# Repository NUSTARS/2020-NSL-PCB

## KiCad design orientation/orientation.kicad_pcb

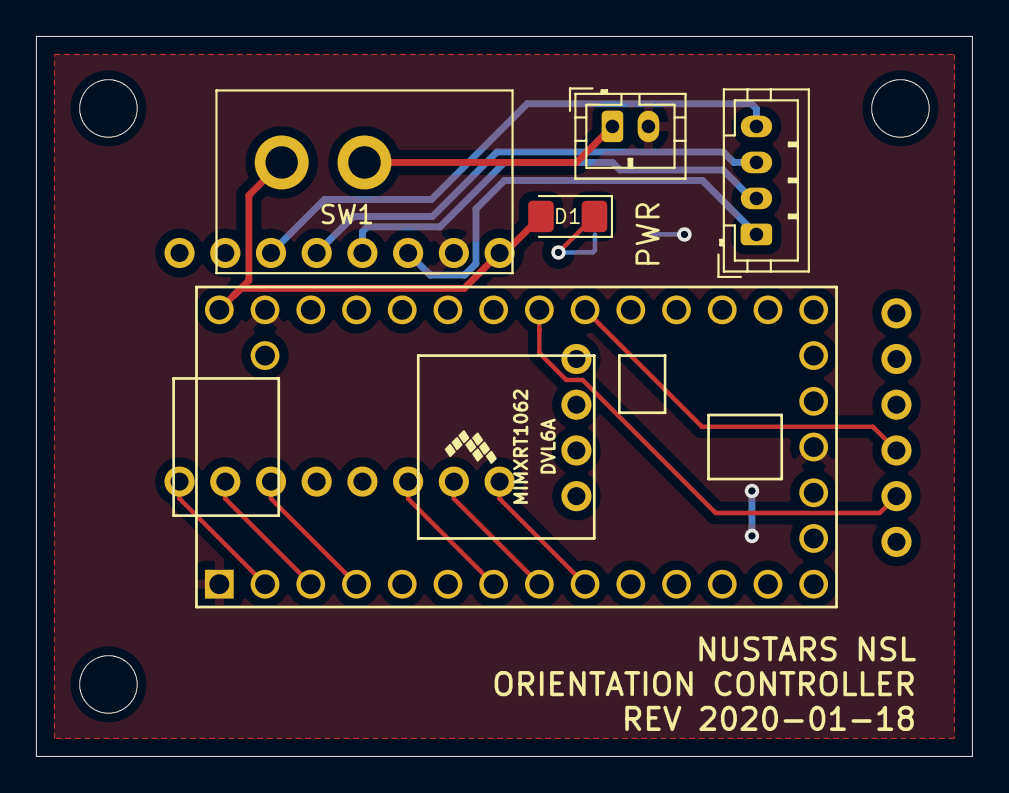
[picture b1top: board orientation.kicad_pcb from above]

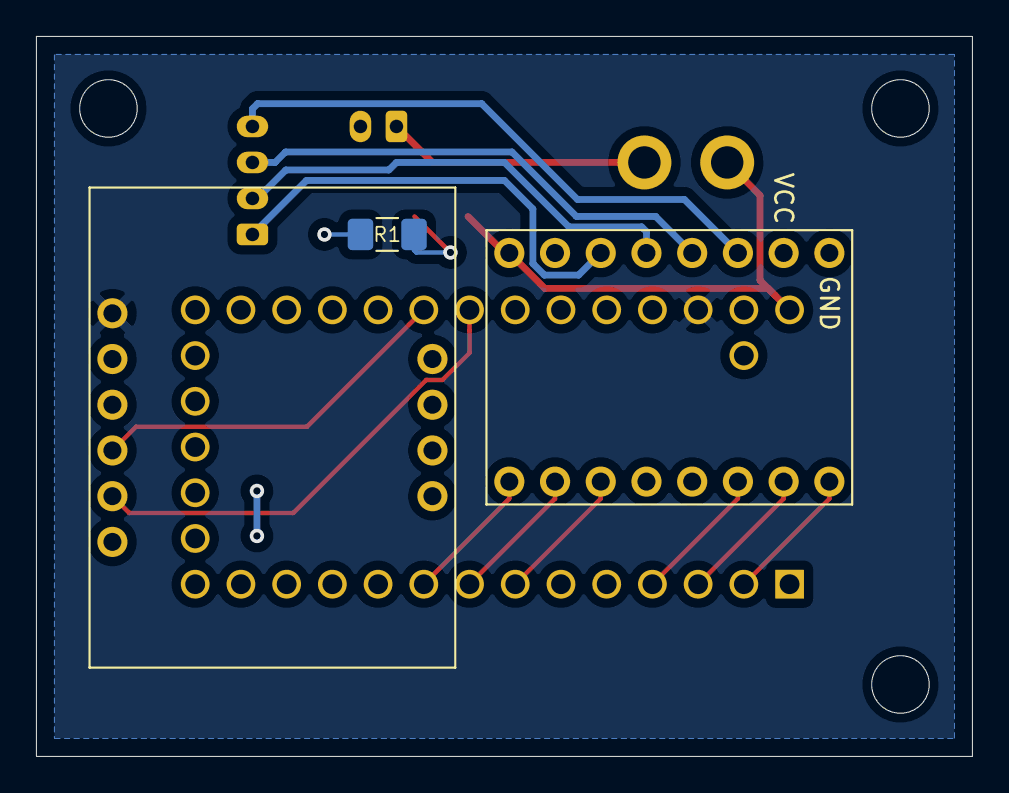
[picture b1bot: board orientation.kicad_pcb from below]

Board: 2 copper layers, 52.0 x 40.0 mm, 8 parts (3 on the bottom side), 17 nets.

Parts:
D1: LED; LED_1206_3216Metric_Pad1.42x1.75mm_HandSolder
J1: Conn_01x02; JST_PH_B2B-PH-K_1x02_P2.00mm_Vertical
J2: Conn_01x04; JST_PH_B4B-PH-K_1x04_P2.00mm_Vertical
R1: 110; R_1206_3216Metric_Pad1.42x1.75mm_HandSolder
SW1: SW_SPST; GF-123-0054
U1: Teensy4.0; Teensy40
U2: STSPIN220
U3: bno055

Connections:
3V3T: U1.31, U3.1
GND: J1.2, R1.2, U1.1, U1.17, U1.32, U2.15
unnamed: D1.1, R1.1
unnamed: J1.1, SW1.1
unnamed: J2.1, U2.14
unnamed: J2.2, U2.13
unnamed: J2.3, U2.12
unnamed: J2.4, U2.11
unnamed: U1.2, U2.8
unnamed: U1.3, U2.7
unnamed: U1.4, U2.6
unnamed: U1.7, U2.3
unnamed: U1.8, U2.2
unnamed: U1.9, U2.1
SCL: U1.26, U3.5
SDA: U1.25, U3.4
VBAT: D1.2, SW1.2, U1.33, U2.16

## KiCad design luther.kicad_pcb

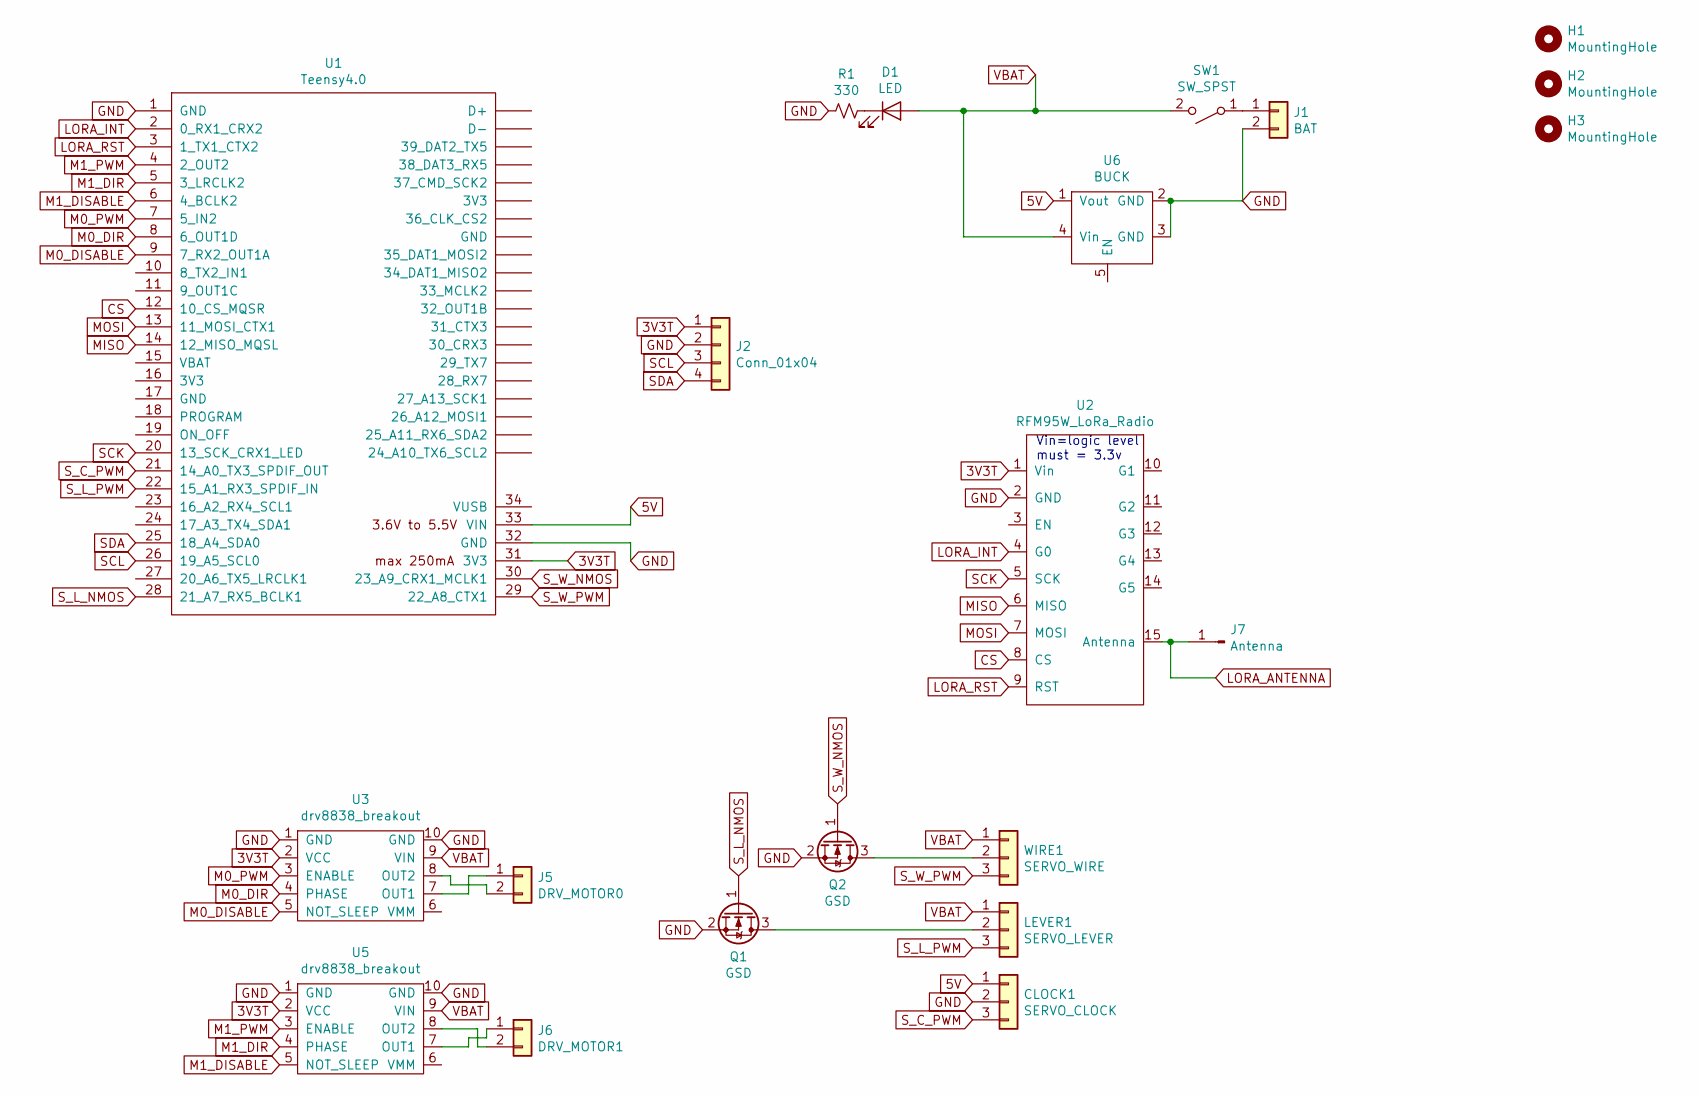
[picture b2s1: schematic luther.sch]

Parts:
CLOCK1: SERVO_CLOCK; JST_PH_B3B-PH-K_1x03_P2.00mm_Vertical
D1: LED; LED_1206_3216Metric_Pad1.42x1.75mm_HandSolder
H1, H2, H3: MountingHole; MountingHole_3.2mm_M3
J1: BAT; DEANS
J2: Conn_01x04; JST_PH_B4B-PH-K_1x04_P2.00mm_Vertical
J5: DRV_MOTOR0; JST_PH_B2B-PH-K_1x02_P2.00mm_Vertical
J6: DRV_MOTOR1; JST_PH_B2B-PH-K_1x02_P2.00mm_Vertical
J7: Antenna
LEVER1: SERVO_LEVER; JST_PH_B3B-PH-K_1x03_P2.00mm_Vertical
Q1, Q2: GSD; SOT-23_Handsoldering
R1: 330; R_1206_3216Metric_Pad1.42x1.75mm_HandSolder
SW1: SW_SPST; GF-123-0054
U1: Teensy4.0; Teensy40
U2: RFM95W_LoRa_Radio; RFM95W
U3, U5: drv8838_breakout
U6: BUCK; D24V50F5
WIRE1: SERVO_WIRE; JST_PH_B3B-PH-K_1x03_P2.00mm_Vertical

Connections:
3V3T: J2.1, U1.31 (3V3), U2.1 (Vin), U3.2 (VCC), U5.2 (VCC)
5V: CLOCK1.1, U1.33 (VIN), U6.1 (Vout)
CS: U1.12 (10_CS_MQSR), U2.8 (CS)
GND: CLOCK1.2, J1.2, J2.2, Q1.2 (S), Q2.2 (S), R1.2, U1.1 (GND), U1.32 (GND), U2.2 (GND), U3.1 (GND), U3.10 (GND), U5.1 (GND), U5.10 (GND), U6.2 (GND), U6.3 (GND)
LORA_ANTENNA: J7.1, U2.15 (Antenna)
LORA_INT: U1.2 (0_RX1_CRX2), U2.4 (G0)
LORA_RST: U1.3 (1_TX1_CTX2), U2.9 (RST)
M0_DIR: U1.8 (6_OUT1D), U3.4 (PHASE)
M0_DISABLE: U1.9 (7_RX2_OUT1A), U3.5 (NOT_SLEEP)
M0_PWM: U1.7 (5_IN2), U3.3 (ENABLE)
M1_DIR: U1.5 (3_LRCLK2), U5.4 (PHASE)
M1_DISABLE: U1.6 (4_BCLK2), U5.5 (NOT_SLEEP)
M1_PWM: U1.4 (2_OUT2), U5.3 (ENABLE)
MISO: U1.14 (12_MISO_MQSL), U2.6 (MISO)
MOSI: U1.13 (11_MOSI_CTX1), U2.7 (MOSI)
unnamed: D1.1 (K), R1.1
unnamed: J1.1, SW1.1 (A)
unnamed: J5.1, U3.7 (OUT1)
unnamed: J5.2, U3.8 (OUT2)
unnamed: J6.1, U5.7 (OUT1)
unnamed: J6.2, U5.8 (OUT2)
unnamed: LEVER1.2, Q1.3 (D)
unnamed: Q2.3 (D), WIRE1.2
SCK: U1.20 (13_SCK_CRX1_LED), U2.5 (SCK)
SCL: J2.3, U1.26 (19_A5_SCL0)
SDA: J2.4, U1.25 (18_A4_SDA0)
S_C_PWM: CLOCK1.3, U1.21 (14_A0_TX3_SPDIF_OUT)
S_L_NMOS: Q1.1 (G), U1.28 (21_A7_RX5_BCLK1)
S_L_PWM: LEVER1.3, U1.22 (15_A1_RX3_SPDIF_IN)
S_W_NMOS: Q2.1 (G), U1.30 (23_A9_CRX1_MCLK1)
S_W_PWM: U1.29 (22_A8_CTX1), WIRE1.3
VBAT: D1.2 (A), LEVER1.1, SW1.2 (B), U3.9 (VIN), U5.9 (VIN), U6.4 (Vin), WIRE1.1

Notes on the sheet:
Vin=logic level must = 3.3v

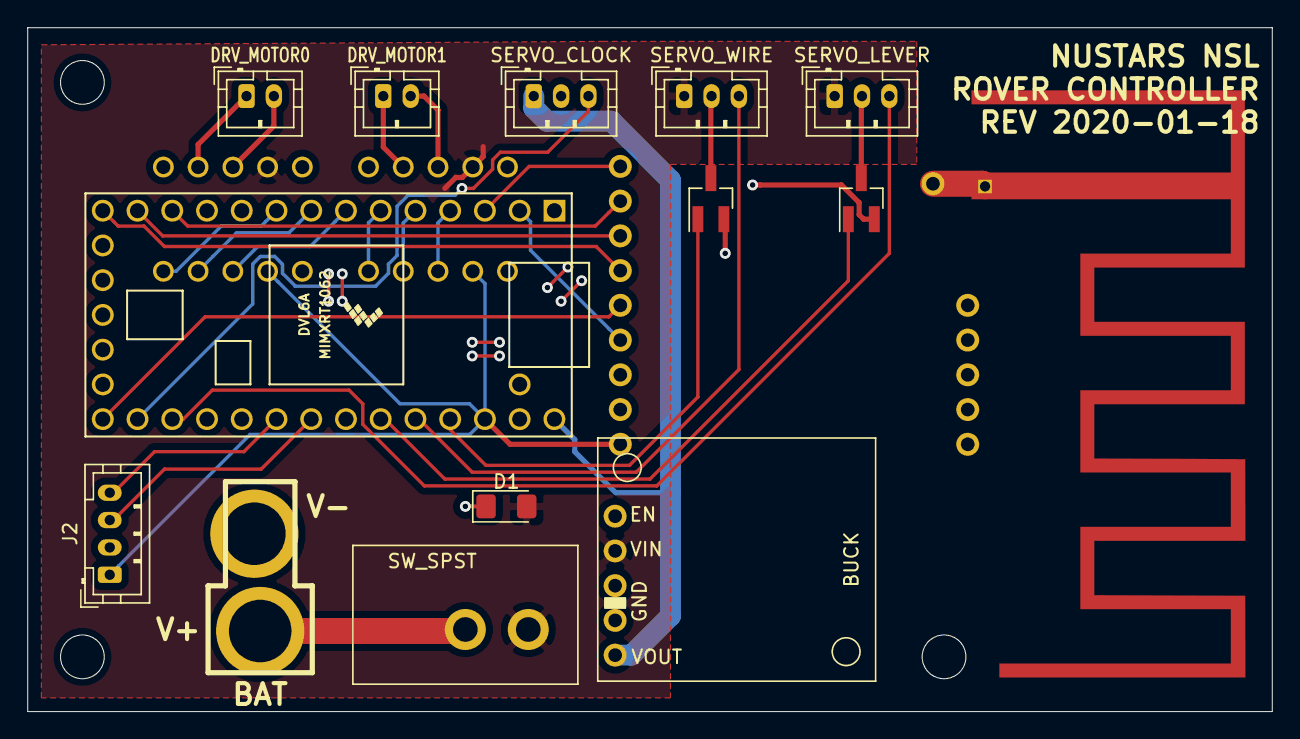
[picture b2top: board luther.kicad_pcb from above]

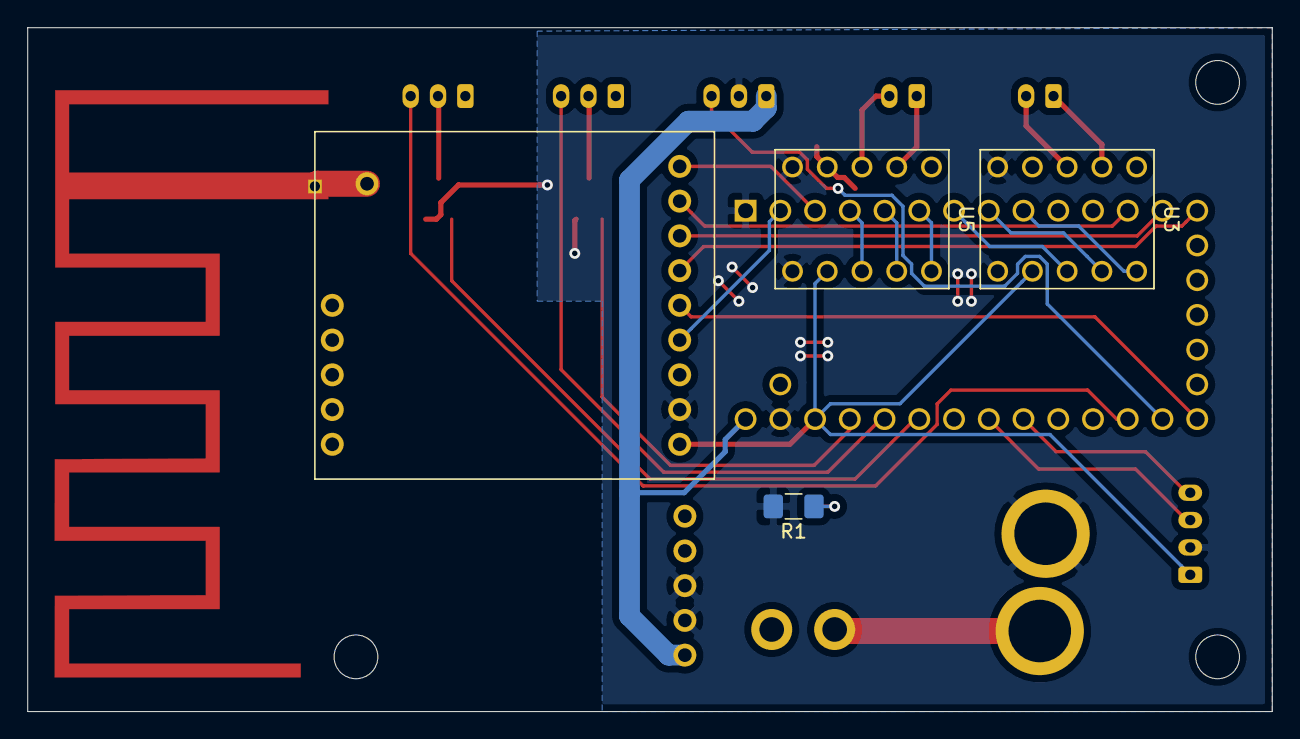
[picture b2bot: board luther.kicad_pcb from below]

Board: 2 copper layers, 91.0 x 50.0 mm, 21 parts (4 on the bottom side), 32 nets.

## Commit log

2019-11-17 init
2019-11-17 libs dir
2019-11-17 Added the symbol for the radio
2019-11-18 we are RoverBoard now
2019-11-18 add teensy lib
2019-11-25 gitignore
2019-11-25 create initial footprint estimate
2019-11-25 move libs to libs folder
2019-11-25 housekeeping
2019-11-25 add teensy footprint
2019-11-25 try to fix gitingore
2019-11-25 fix gitignore
2019-11-25 finish add teesny footprint
2019-12-14 hc-sr04 footprint
2019-12-15 FONA808
2019-12-15 sike no FONA808
2019-12-15 FONA808 (I hope)
2019-12-15 FONA808 ??
    idk if necessary
2019-12-15 FONA808 ???
    may not be necessary pt 2
2019-12-18 Add Adafruit SIM808 library to library list for symbols
2019-12-28 Some FONA808 stuff
    I was gonna update the netlist on the PCB but then it said the changes you make cannot be undone and that psyched me out a little so I didn't but that seems like a good thing to do at some point perh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
2020-01-03 add newline to .gitignore
2020-01-03 ammend gitignore
2020-01-03 remove bak file from repo
2020-01-03 VNH5019 symbol and footprint
2020-01-03 bno symbol
2020-01-03 add schema for lora, teensy, fona
2020-01-08 add switch to orientation board
2020-01-08 misc changes
2020-01-12 Added Antenna
2020-01-12 schematic/footprint for drv8838 motor driver
2020-01-19 prelim finish sans decor
2020-01-19 baby luther
2020-01-19 add GND and 3.3V connections on orientation
2020-02-16 Orientation !!
